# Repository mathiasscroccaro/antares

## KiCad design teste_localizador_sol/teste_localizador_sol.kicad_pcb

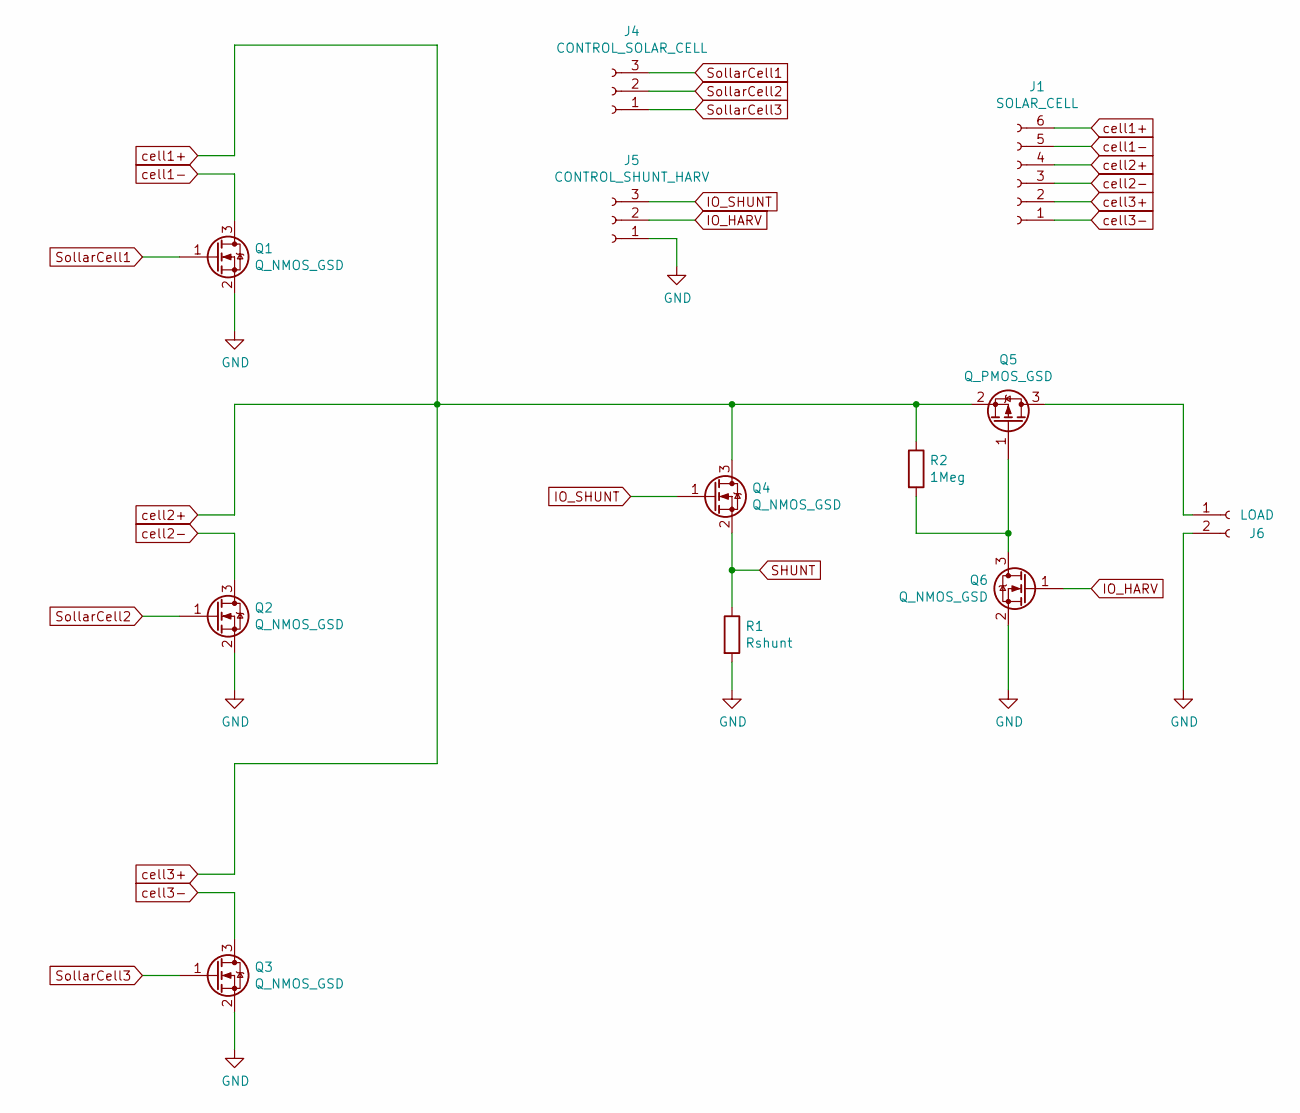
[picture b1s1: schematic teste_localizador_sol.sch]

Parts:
J1: SOLAR_CELL; PinSocket_1x06_P2.54mm_Vertical
J4: CONTROL_SOLAR_CELL; PinHeader_1x03_P2.54mm_Vertical
J5: CONTROL_SHUNT_HARV; PinHeader_1x03_P2.54mm_Vertical
J6: LOAD; PinSocket_2x01_P2.54mm_Vertical
Q1, Q2, Q3, Q4, Q6: Q_NMOS_GSD; SOT-23
Q5: Q_PMOS_GSD; SOT-23
R1: Rshunt; PinSocket_2x01_P2.54mm_Vertical
R2: 1Meg; R_Axial_DIN0411_L9.9mm_D3.6mm_P15.24mm_Horizontal

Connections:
GND: J5.1, J6.2, Q1.2 (S), Q2.2 (S), Q3.2 (S), Q6.2 (S), R1.2
IO_HARV: J5.2, Q6.1 (G)
IO_SHUNT: J5.3, Q4.1 (G)
unnamed: J6.1, Q5.3 (D)
unnamed: Q5.1 (G), Q6.3 (D), R2.2
SHUNT: Q4.2 (S), R1.1
SollarCell1: J4.3, Q1.1 (G)
SollarCell2: J4.2, Q2.1 (G)
SollarCell3: J4.1, Q3.1 (G)
cell1+: J1.2, J1.4, J1.6, Q4.3 (D), Q5.2 (S), R2.1
cell1-: J1.5, Q1.3 (D)
cell2-: J1.3, Q2.3 (D)
cell3-: J1.1, Q3.3 (D)

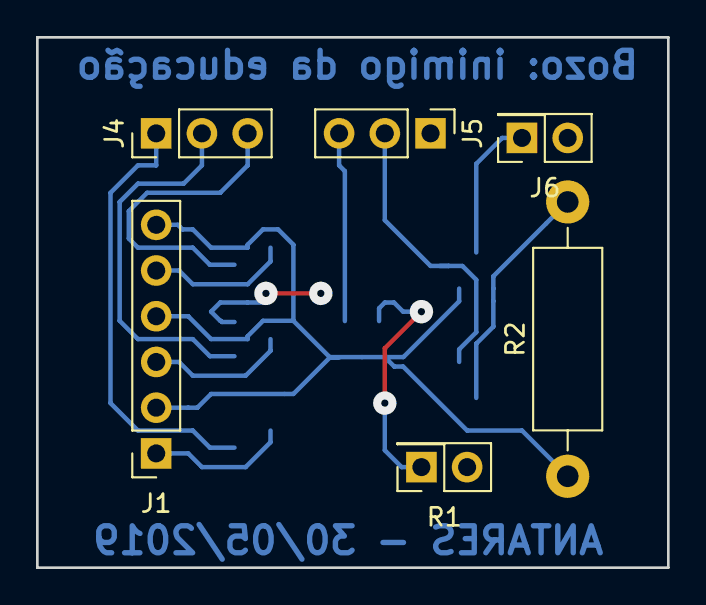
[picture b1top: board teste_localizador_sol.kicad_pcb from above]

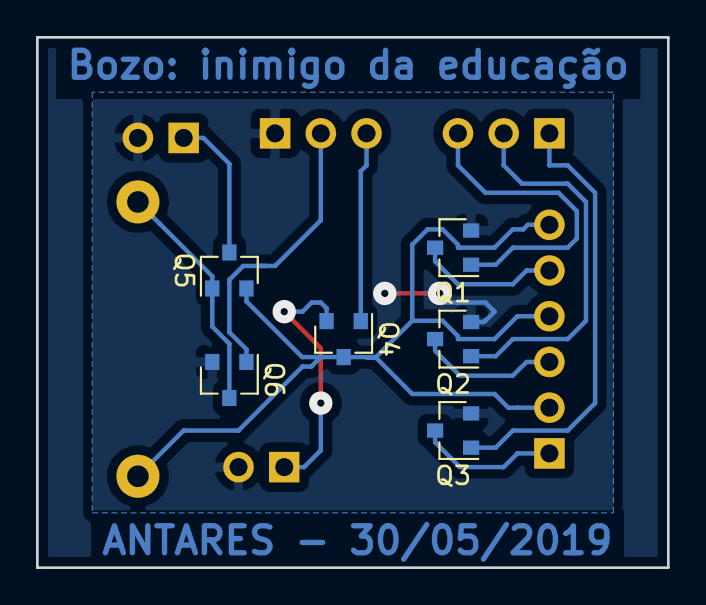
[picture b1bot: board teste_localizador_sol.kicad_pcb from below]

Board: 2 copper layers, 35.1 x 29.5 mm, 12 parts (6 on the bottom side), 13 nets.

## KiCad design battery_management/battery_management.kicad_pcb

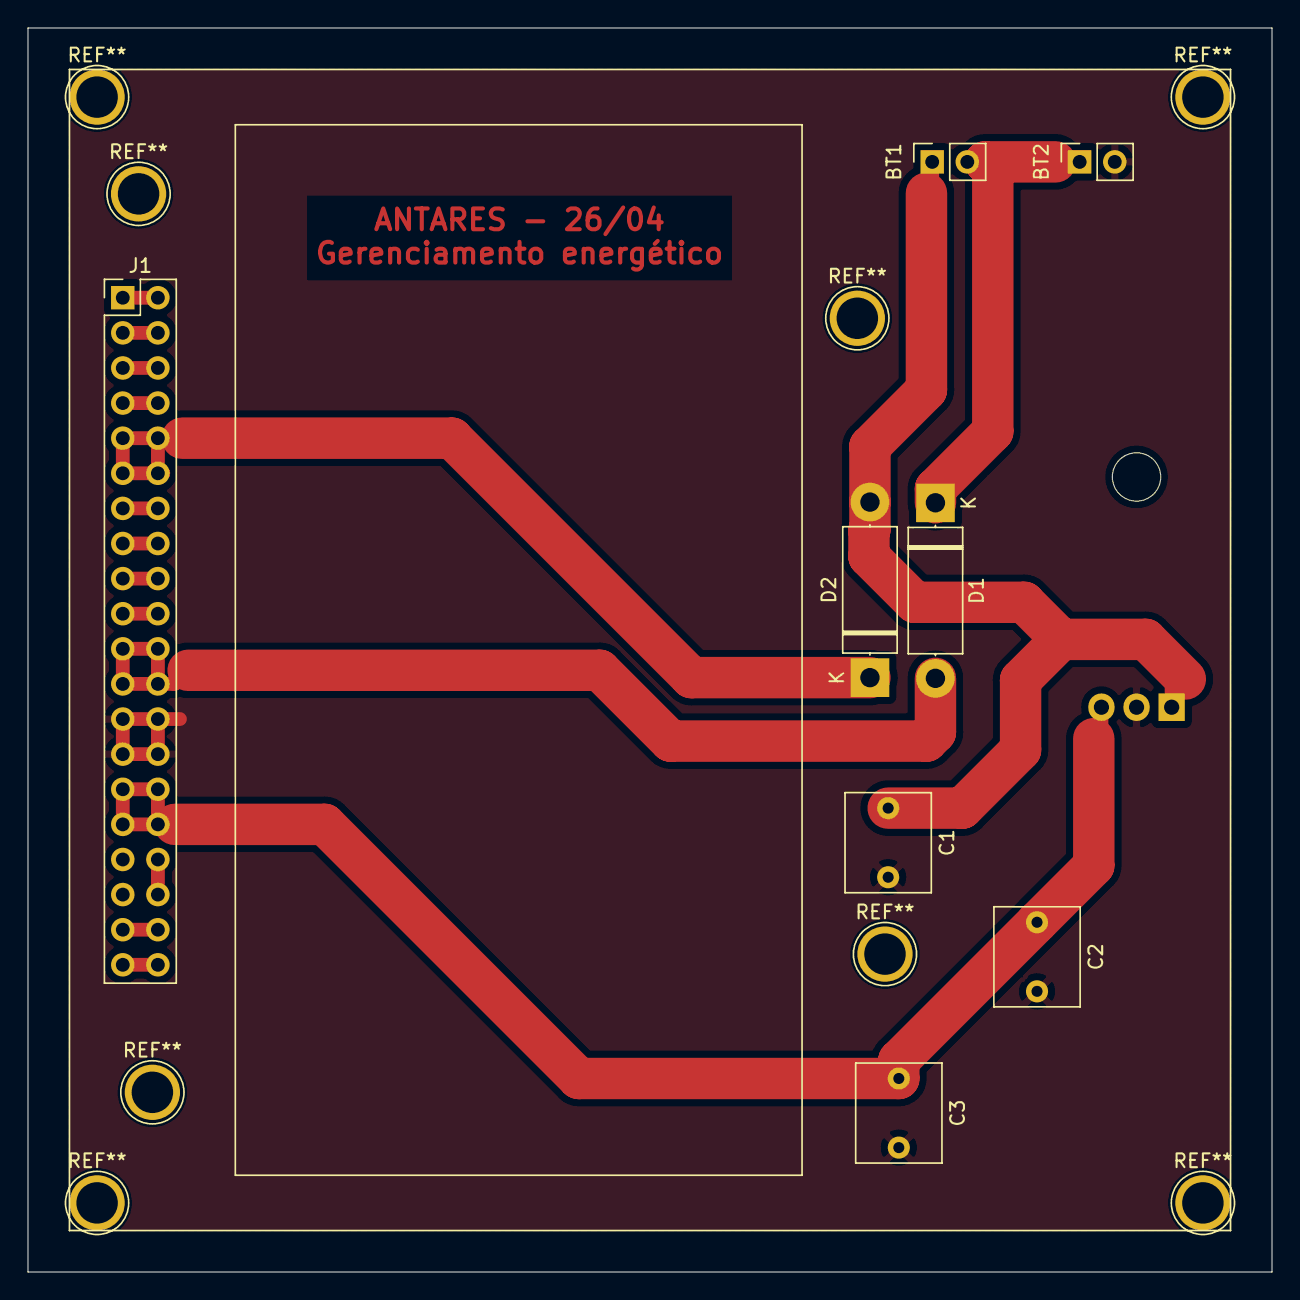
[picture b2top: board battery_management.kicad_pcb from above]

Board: 2 copper layers, 90.0 x 90.0 mm, 9 parts (1 on the bottom side), 17 nets.

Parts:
BT1, BT2: Battery_Cell; PinSocket_1x02_P2.54mm_Vertical
C1: 0.33uF; C_Rect_L7.0mm_W6.0mm_P5.00mm
C2: 100nF; C_Rect_L7.0mm_W6.0mm_P5.00mm
C3: 20uF; C_Rect_L7.0mm_W6.0mm_P5.00mm
D1, D2: D; D_5W_P12.70mm_Horizontal
J1: Conn_02x20_Odd_Even; PinHeader_2x20_P2.54mm_Vertical
U1: L7805; TO-220-3_Horizontal_TabDown

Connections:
FG-BLDC-OUT: J1.37, J1.38
GND: BT2.2, C1.2, C2.2, C3.2, J1.25, J1.26, J1.27, J1.28, U1.2
INV-BLDC: J1.34, J1.36
IO1: J1.7, J1.8
IO2: J1.5, J1.6
IO3: J1.3, J1.4
IO4: J1.1, J1.2
IO5: J1.13, J1.14
IO6: J1.15, J1.16
IO7: J1.17, J1.18
IO8: J1.19, J1.20
unnamed: BT1.1, C1.1, D2.2, U1.1
unnamed: BT1.2, BT2.1, D1.1
PWM-BLDC: J1.39, J1.40
VBAT: D2.1, J1.9, J1.10, J1.11, J1.12
VHARV: D1.2, J1.21, J1.22, J1.23, J1.24
VIN-5V: C2.1, C3.1, J1.29, J1.30, J1.31, J1.32, U1.3

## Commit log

2019-04-26 Layout to SPE pronto
2019-04-30 esquemático semi-pronto v0.2
2019-04-30 layout da primeira versao commitado
2019-05-31 Circuito de teste para localização do sol prototipado, falta testá-lo
